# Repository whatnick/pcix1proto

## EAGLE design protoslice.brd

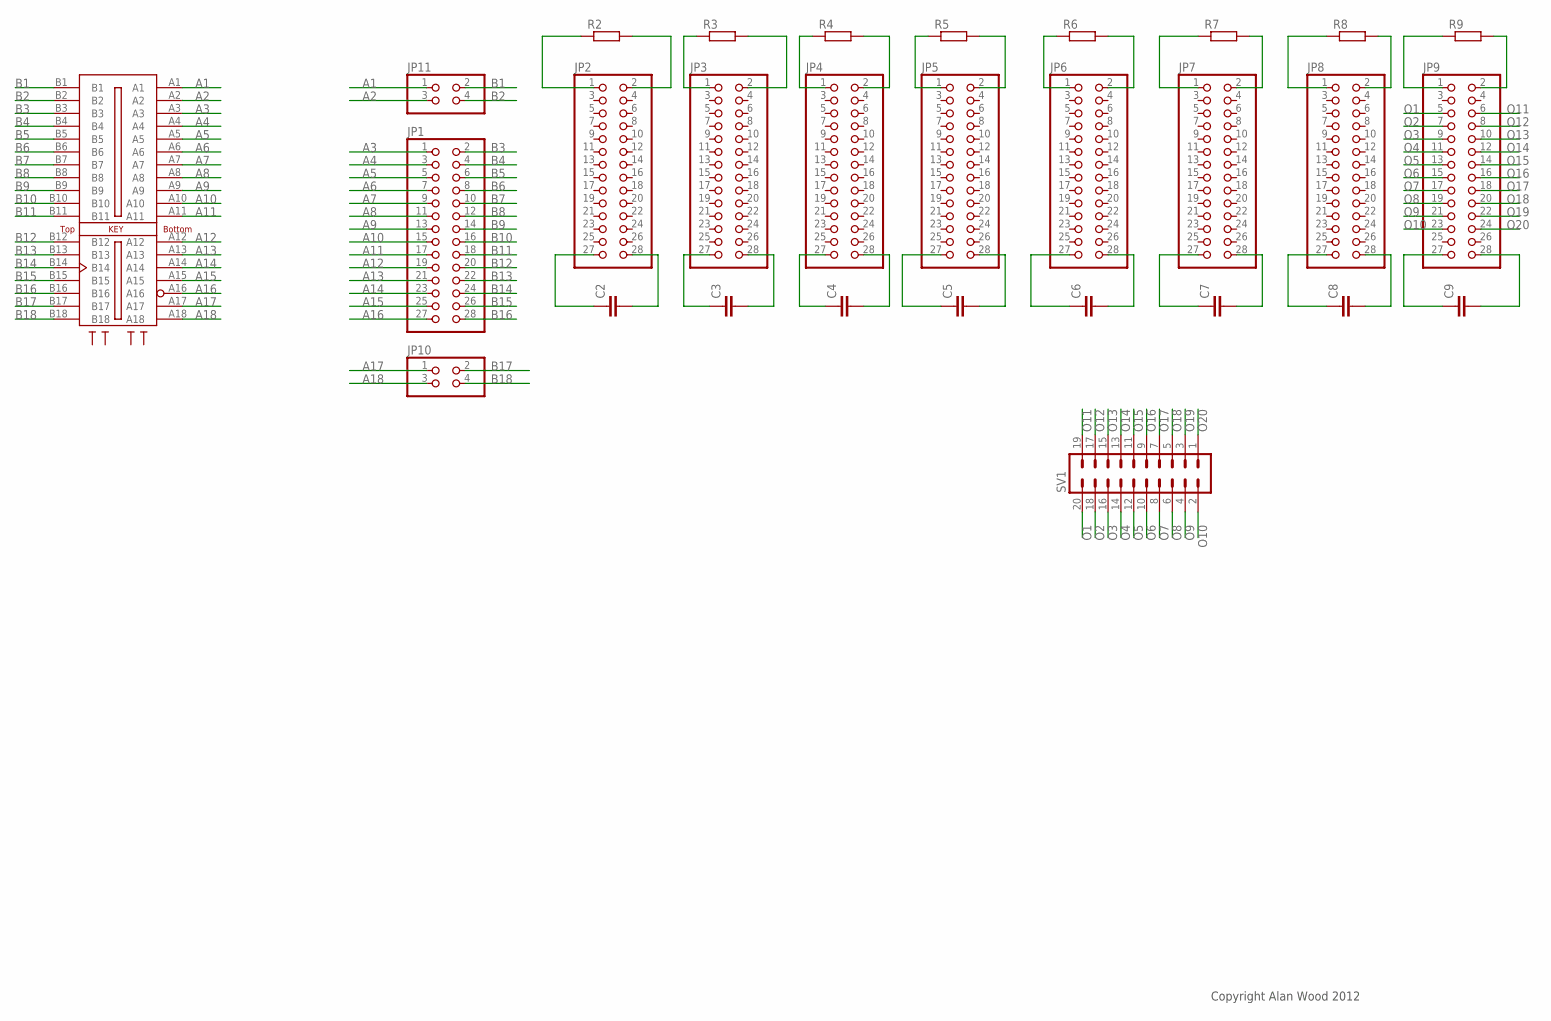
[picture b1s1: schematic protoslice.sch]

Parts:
C2, C3, C4, C5, C6, C7, C8, C9: C-EUC0805; C0805
JP1, JP2, JP3, JP4, JP5, JP6, JP7, JP8, JP9: PINHD-2X14; 2X14
JP10, JP11: PINHD-2X2; 2X02
R2, R3, R4, R5, R6, R7, R8, R9: R-EU_R0805; R0805
SV1: MA10-2W
U$1: XSLICE

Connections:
A1: JP11.1, U$1.A1
A2: JP11.3, U$1.A2
A3: JP1.1, U$1.A3
A4: JP1.3, U$1.A4
A5: JP1.5, U$1.A5
A6: JP1.7, U$1.A6
A7: JP1.9, U$1.A7
A8: JP1.11, U$1.A8
A9: JP1.13, U$1.A9
A10: JP1.15, U$1.A10
A11: JP1.17, U$1.A11
A12: JP1.19, U$1.A12
A13: JP1.21, U$1.A13
A14: JP1.23, U$1.A14
A15: JP1.25, U$1.A15
A16: JP1.27, U$1.A16
A17: JP10.1, U$1.A17
A18: JP10.3, U$1.A18
B1: JP11.2, U$1.B1
B2: JP11.4, U$1.B2
B3: JP1.2, U$1.B3
B4: JP1.4, U$1.B4
B5: JP1.6, U$1.B5
B6: JP1.8, U$1.B6
B7: JP1.10, U$1.B7
B8: JP1.12, U$1.B8
B9: JP1.14, U$1.B9
B10: JP1.16, U$1.B10
B11: JP1.18, U$1.B11
B12: JP1.20, U$1.B12
B13: JP1.22, U$1.B13
B14: JP1.24, U$1.B14
B15: JP1.26, U$1.B15
B16: JP1.28, U$1.B16
B17: JP10.2, U$1.B17
B18: JP10.4, U$1.B18
unnamed: JP2.1, R2.1
unnamed: JP2.2, R2.2
unnamed: C2.1, JP2.27
unnamed: C2.2, JP2.28
unnamed: JP3.1, R3.1
unnamed: JP3.2, R3.2
unnamed: JP4.1, R4.1
unnamed: JP4.2, R4.2
unnamed: JP5.1, R5.1
unnamed: JP5.2, R5.2
unnamed: JP6.1, R6.1
unnamed: JP6.2, R6.2
unnamed: JP7.1, R7.1
unnamed: JP7.2, R7.2
unnamed: C7.1, JP7.27
unnamed: C7.2, JP7.28
unnamed: C6.2, JP6.28
unnamed: C6.1, JP6.27
unnamed: C5.2, JP5.28
unnamed: C5.1, JP5.27
unnamed: C4.2, JP4.28
unnamed: C4.1, JP4.27
unnamed: C3.2, JP3.28
unnamed: C3.1, JP3.27
unnamed: JP8.1, R8.1
unnamed: JP8.2, R8.2
unnamed: C8.1, JP8.27
unnamed: C8.2, JP8.28
unnamed: C9.1, JP9.27
unnamed: C9.2, JP9.28
unnamed: JP9.1, R9.1
unnamed: JP9.2, R9.2
O1: JP9.5, SV1.20
O2: JP9.7, SV1.18
O3: JP9.9, SV1.16
O4: JP9.11, SV1.14
O5: JP9.13, SV1.12
O6: JP9.15, SV1.10
O7: JP9.17, SV1.8
O8: JP9.19, SV1.6
O9: JP9.21, SV1.4
O10: JP9.23, SV1.2
O11: JP9.6, SV1.19
O12: JP9.8, SV1.17
O13: JP9.10, SV1.15
O14: JP9.12, SV1.13
O15: JP9.14, SV1.11
O16: JP9.16, SV1.9
O17: JP9.18, SV1.7
O18: JP9.20, SV1.5
O19: JP9.22, SV1.3
O20: JP9.24, SV1.1

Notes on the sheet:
Copyright Alan Wood 2012

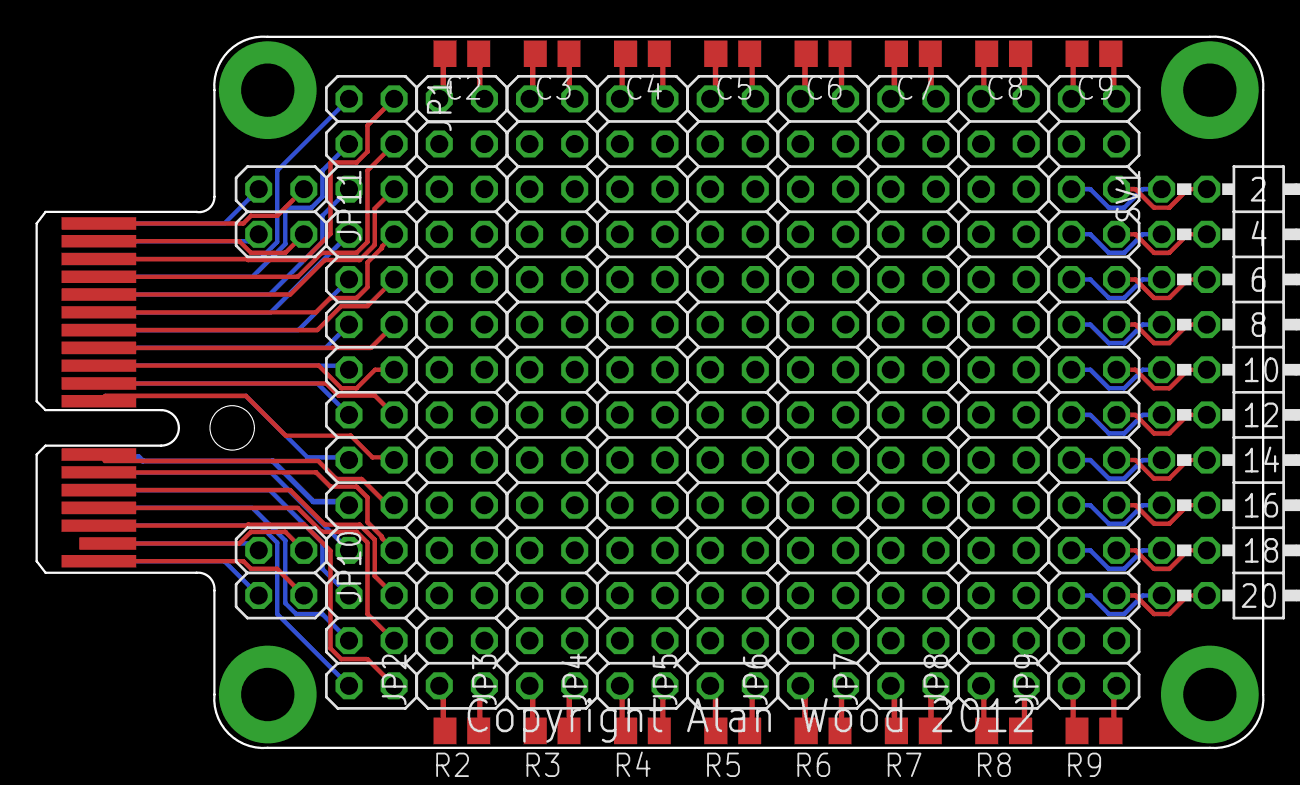
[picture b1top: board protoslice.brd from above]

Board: 2 copper layers, 69.0 x 40.0 mm, 29 parts (0 on the bottom side), 88 nets.

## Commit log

2012-10-26 Added initial components
2012-10-26 Added passive components
2017-10-07 Made for energy monitor proto
2017-10-07 removed random line
